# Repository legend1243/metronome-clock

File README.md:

# Metronome Clock for Musicians

A pocket-sized digital metronome powered by the **ATtiny412**, featuring a 1.3-inch monochrome OLED display and simple physical controls.

---

## Features

- **ATtiny412 Microcontroller** — Compact AVR microcontroller handling the metronome and user interface.
- **OLED Display** — 1.3-inch monochrome I²C display for visual feedback and interface.
- **Physical Controls** — Simple button and potentiometer-based input.
- **Piezoelectric Buzzer** — Provides audible metronome beats.
- **AAA Battery Powered** — Operates using two standard AAA batteries.
- **UPDI Programming** — Supports firmware programming and experimentation through the UPDI interface.
- **Custom PCB** — Designed and developed using KiCad.

## Hardware

| Component       | Description                  |
| :---            | :---                         |
| Microcontroller | ATtiny412                    |
| Display         | 1.3-inch I²C Monochrome OLED |
| Input           | 1× Push Button               |
| Input           | 1× Potentiometer             |
| Sound           | 1× Piezoelectric Buzzer      |
| Power           | 2× AAA Batteries             |
| Programming     | UPDI                         |

## Gallery

### Schematics

### PCB Design

## Firmware

The firmware implements a simple metronome interface with accessible physical controls.

The ATtiny412's UPDI programming interface also allows compatible firmware to be flashed onto the microcontroller, making it possible to experiment with additional custom applications.

## PCB Design

The schematic and PCB layout were designed using **KiCad**.

All project design files and development documentation are maintained in this repository.

## Development Journal

Follow the project's engineering progress, design decisions, technical challenges, and development milestones in [LOG.md](LOG.md).

---

**Designed by legend1243 (Chen E-Chen)**

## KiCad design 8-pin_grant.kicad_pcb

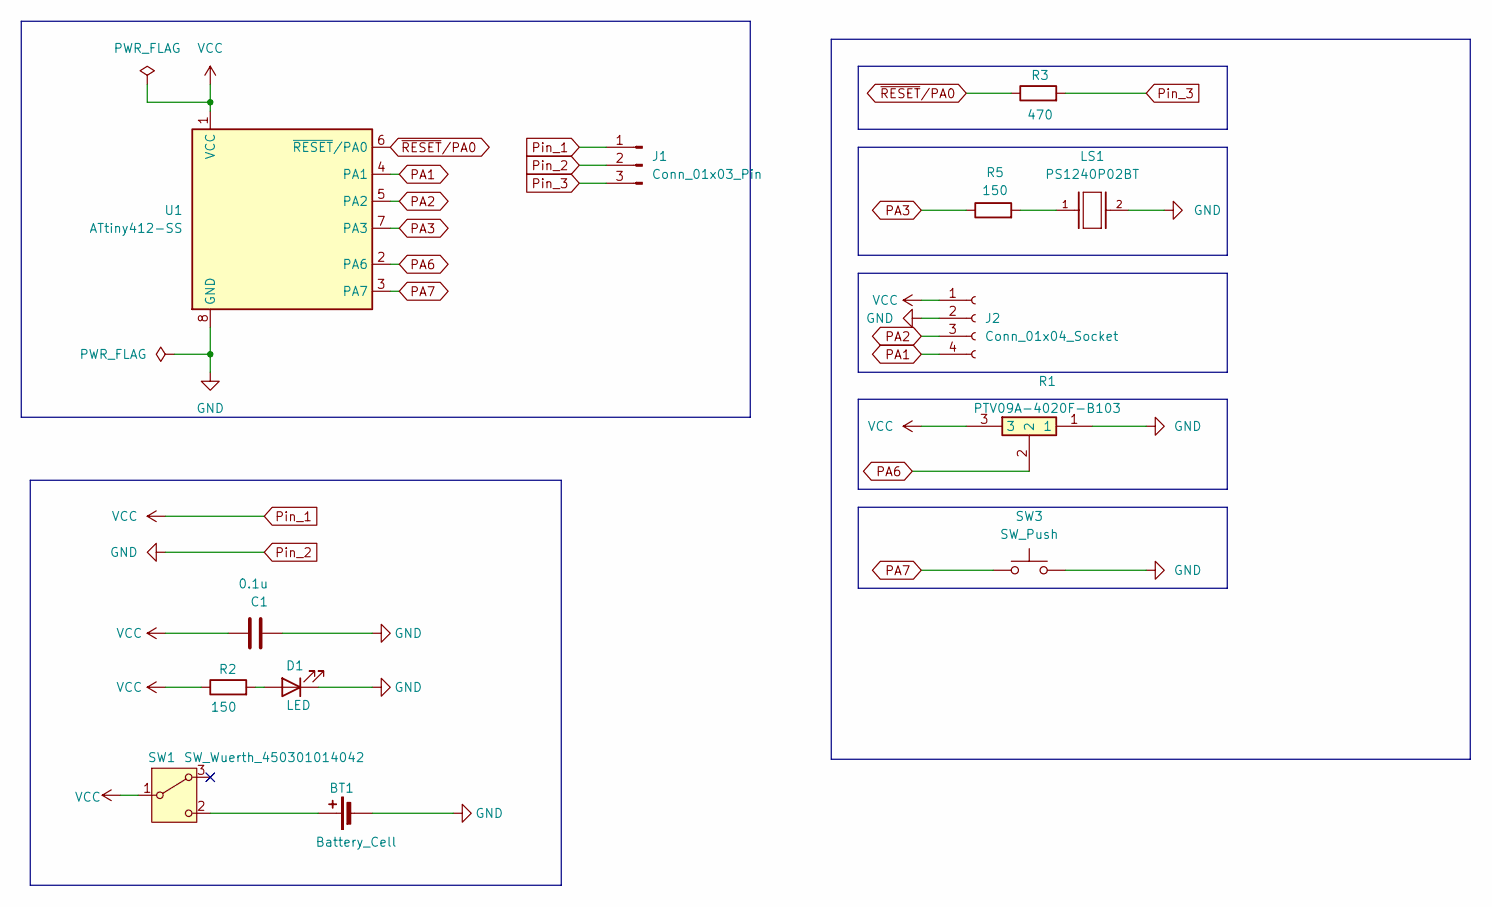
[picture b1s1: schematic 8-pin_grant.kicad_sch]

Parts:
BT1: Battery_Cell; BatteryHolder_Keystone_2468_2xAAA
C1: 0.1u; C_0805_2012Metric
D1: LED; LED_0805_2012Metric
J1: Conn_01x03_Pin; PinHeader_1x03_P2.54mm_Vertical
J2: Conn_01x04_Socket; PinSocket_1x04_P2.54mm_Vertical
LS1: PS1240P02BT; XDCR_PS1240P02BT; MPN PS1240P02BT
R1: PTV09A-4020F-B103; PTV09A4020FB103; Manufacturer_Part_Number PTV09A-4020F-B103; Mouser Part Number 652-PTV09A-4020FB103
R2, R5: 150; R_0805_2012Metric
R3: 470; R_0805_2012Metric
SW1: SW_Wuerth_450301014042; SW_Slide-03_Wuerth-WS-SLTV_10x2.5x6.4_P2.54mm
SW3: SW_Push; SW_SPST_B3U-1000P
U1: ATtiny412-SS; SOIC-8_3.9x4.9mm_P1.27mm

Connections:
unnamed: BT1.1 (+), SW1.2 (C)
unnamed: D1.2 (A), R2.2
unnamed: LS1.1, R5.2
PA1: J2.4, U1.4 (PA1)
PA2: J2.3, U1.5 (PA2)
PA3: R5.1, U1.7 (PA3)
PA6: R1.2, U1.2 (PA6)
PA7: SW3.1, U1.3 (PA7)
Pin_1: C1.1, J1.1, J2.1, R1.3, R2.1, SW1.1 (B), U1.1 (VCC)
Pin_2: BT1.2 (-), C1.2, D1.1 (K), J1.2, J2.2, LS1.2, R1.1, SW3.2, U1.8 (GND)
Pin_3: J1.3, R3.2
~RESET/PA0: R3.1, U1.6 (~RESET/PA0)

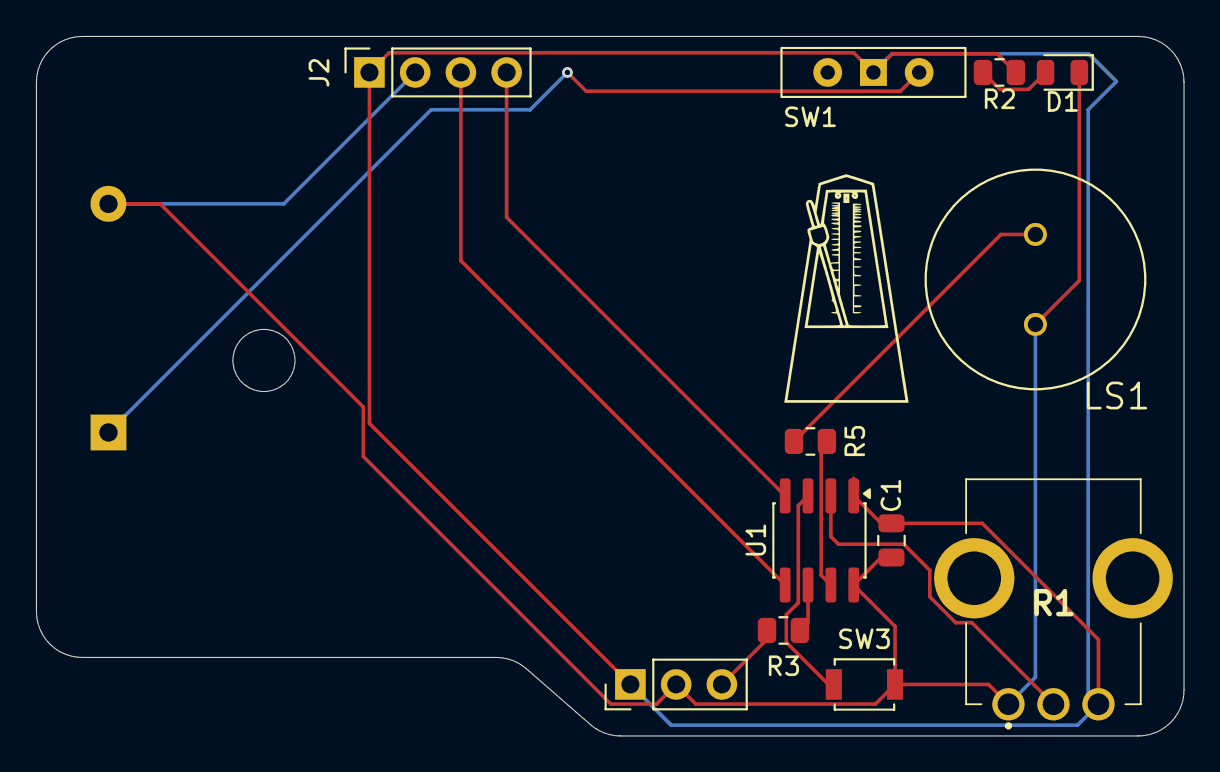
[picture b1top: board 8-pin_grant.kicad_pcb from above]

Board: 2 copper layers, 63.8 x 38.9 mm, 13 parts (1 on the bottom side), 12 nets.

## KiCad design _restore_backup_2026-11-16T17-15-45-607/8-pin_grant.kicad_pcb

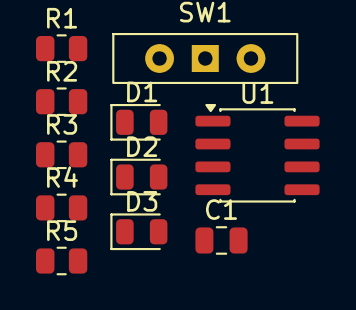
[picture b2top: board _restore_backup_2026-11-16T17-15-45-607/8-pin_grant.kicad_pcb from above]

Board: 2 copper layers, 11 parts (0 on the bottom side), 9 nets, no tracks yet.

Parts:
C1: 0.1u; C_0805_2012Metric
D1, D2, D3: LED; LED_0805_2012Metric
R1, R2, R4, R5: 150; R_0805_2012Metric
R3: 470; R_0805_2012Metric
SW1: SW_Wuerth_450301014042; SW_Slide-03_Wuerth-WS-SLTV_10x2.5x6.4_P2.54mm
U1: ATtiny412-SS; SOIC-8_3.9x4.9mm_P1.27mm

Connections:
unnamed: D1.2 (A), R2.2
unnamed: D2.2 (A), R1.2
unnamed: D3.2 (A), R4.2
PA1: R1.1, U1.4 (PA1)
PA2: R4.1, U1.5 (PA2)
PA3: R5.1, U1.7 (PA3)
Pin_1: C1.1, R2.1, SW1.1 (B), U1.1 (VCC)
Pin_2: C1.2, D1.1 (K), D2.1 (K), D3.1 (K), U1.8 (GND)
~RESET/PA0: R3.1, U1.6 (~RESET/PA0)
